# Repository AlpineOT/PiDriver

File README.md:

# PiDriver
KiCad Raspberry Pi Solenoid Driver Board

Alpine designed this RPi add-on board to drive solenoids for test automation; however, it's a generic 10-channel MOSFET board that could also be used to drive relays, LEDS, DC motors, etc.

## Features

* Controls up to 10 solenoids (though the number that can be simultaneously activated will depend upon the solenoid and capacity of your power supply)
* 2 of the 10 channels have PWM capability
* Designed for a 9-24V power input and, thus, 9-24V solenoids
* On-board flyback protection for inductive loads
* Designed for fast solenoid switching

## Fabrication

See the README_FAB.txt for notes on how the board is fabricated. Fabrication packages can be found on the [Releases](https://github.com/AlpineOT/PiDriver/releases) tab in the Github repo.

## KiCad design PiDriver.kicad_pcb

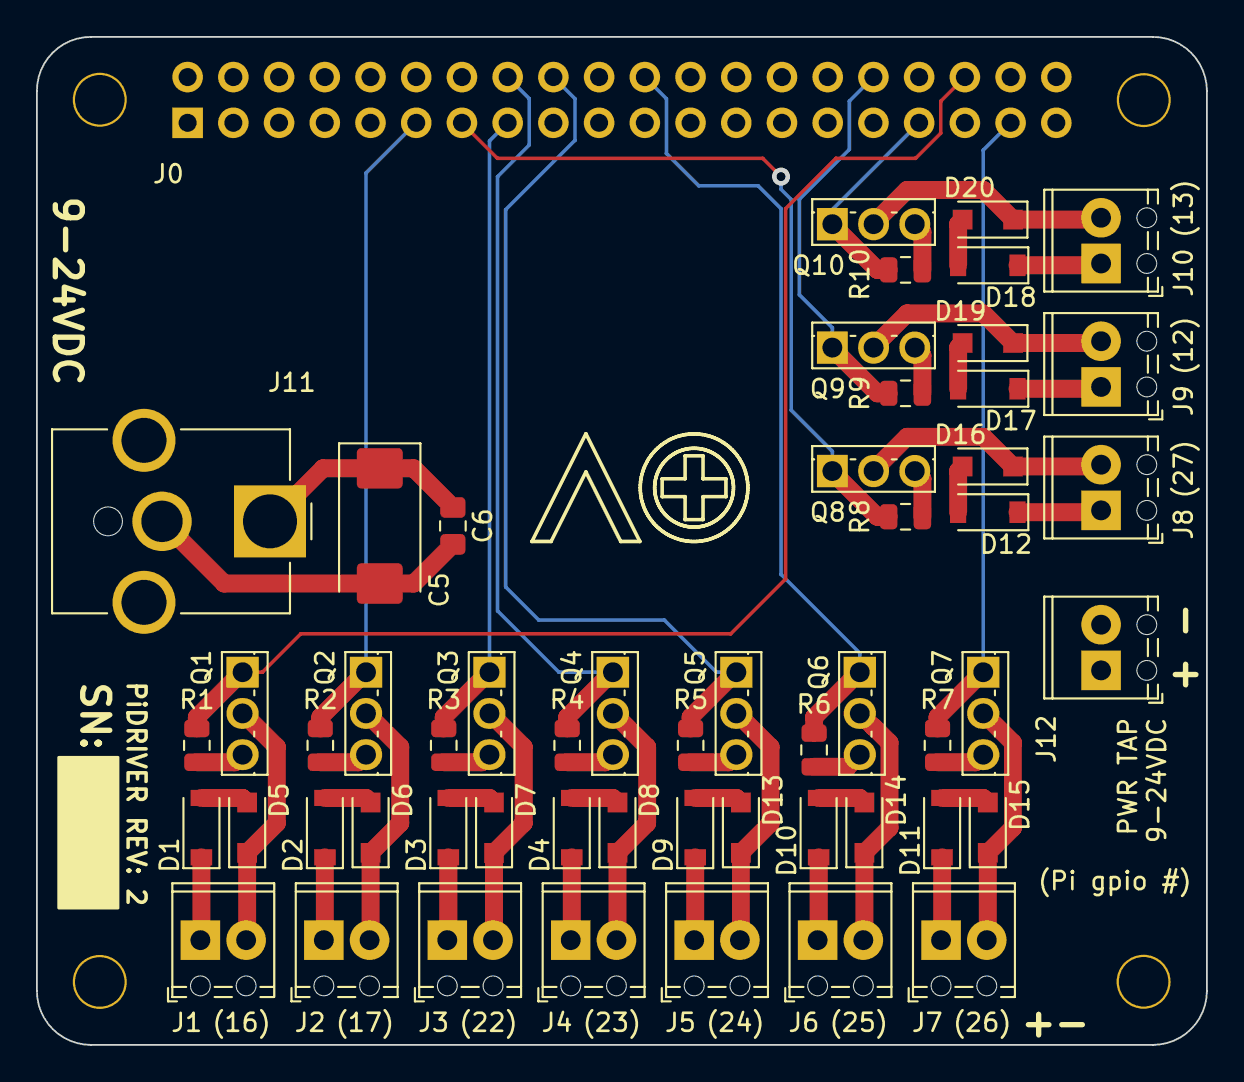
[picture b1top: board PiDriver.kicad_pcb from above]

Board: 4 copper layers, 65.0 x 56.0 mm, 60 parts (1 on the bottom side), 32 nets.

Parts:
C5: 100uF; CP_EIA-7343-43_Kemet-X_Pad2.25x2.55mm_HandSolder
C6: DNP; C_0805_2012Metric_Pad1.15x1.40mm_HandSolder
D1, D2, D3, D4, D9, D10, D11, D12, D17, D18: 1N4448W; D_SOD-123
D5, D6, D7, D8, D13, D14, D15, D16, D19, D20: DZ2W39000L; D_SOD-123F
J0: Raspberry_Pi_2_3; PinSocket_2x20_P2.54mm_Vertical
J1, J2, J3, J4, J5, J6, J7, J8, J9, J10, J12: Screw_Terminal_01x02; TerminalBlock_Phoenix_MPT-0,5-2-2.54_1x02_P2.54mm_Horizontal
J11: Jack-DC; BarrelJack_CUI_PJ-063AH_Horizontal_CircularHoles
LOGO1: AlpineLogo
MH1, MH2, MH3, MH4: MountingHole; NPTH_3mm_ID
Q1, Q2, Q3, Q4, Q5, Q6, Q7, Q8, Q9, Q10: IRLU024NPBF; TO-251-3_Vertical
R1, R2, R3, R4, R5, R6, R7, R8, R9, R10: 47K; R_0805_2012Metric

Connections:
/DRIVER_1: J0.36, Q1.1, R1.1
/DRIVER_2: J0.11, Q2.1, R2.1
/DRIVER_3: J0.15, Q3.1, R3.1
/DRIVER_4: J0.16, Q4.1, R4.1
/DRIVER_5: J0.18, Q5.1, R5.1
/DRIVER_6: J0.22, Q6.1, R6.1
/DRIVER_7: J0.37, Q7.1, R7.1
/DRIVER_8: J0.13, Q8.1, R8.1
/DRIVER_9: J0.32, Q9.1, R9.1
/DRIVER_10: J0.33, Q10.1, R10.1
GND: C5.2, C6.2, J0.6, J0.9, J0.14, J0.20, J0.25, J0.30, J0.34, J0.39, J11.2, J12.2, Q1.3, Q2.3, Q3.3, Q4.3, Q5.3, Q6.3, Q7.3, Q8.3, Q9.3, Q10.3, R1.2, R2.2, R3.2, R4.2, R5.2, R6.2, R7.2, R8.2, R9.2, R10.2
unnamed: D1.2, D5.2
unnamed: D2.2, D6.2
unnamed: D3.2, D7.2
unnamed: D4.2, D8.2
unnamed: D5.1, J1.2, Q1.2
unnamed: D6.1, J2.2, Q2.2
unnamed: D7.1, J3.2, Q3.2
unnamed: D8.1, J4.2, Q4.2
unnamed: D10.2, D14.2
unnamed: D11.2, D15.2
unnamed: D12.2, D16.2
unnamed: D13.1, J5.2, Q5.2
unnamed: D9.2, D13.2
unnamed: D14.1, J6.2, Q6.2
unnamed: D15.1, J7.2, Q7.2
unnamed: D16.1, J8.2, Q8.2
unnamed: D17.2, D19.2
unnamed: D18.2, D20.2
unnamed: D19.1, J9.2, Q9.2
unnamed: D20.1, J10.2, Q10.2
VCC: C5.1, C6.1, D1.1, D2.1, D3.1, D4.1, D9.1, D10.1, D11.1, D12.1, D17.1, D18.1, J1.1, J2.1, J3.1, J4.1, J5.1, J6.1, J7.1, J8.1, J9.1, J10.1, J11.1, J12.1

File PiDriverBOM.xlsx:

PCBA Name: |  | PiDriver
PCBA Revision: |  | 2
Item # | Quantity | Reference Designator | Manufacturer | Manufacturer Part Number | Description/Value | Vendor | Vendor Part Number | Notes
1 | 1 | C5 | KEMET | T491X107K025AT | CAP TANT 100UF 25V 10% 2917 | Digikey | 399-8410-1-ND
2 | 1 | C6 | DNP | DNP | DNP | DNP | DNP | DNP
3 | 10 | D1, D2, D3, D4, D9, D10, D11, D12, D17, D18 | Micro Commercial Co | 1N4448W-TP | DIODE GEN PURP 75V 250MA SOD123 | Digikey | 1N4448WTPMSCT-ND
4 | 10 | D5, D6, D7, D8, D13, D14, D15, D16, D19, D20 | Panasonic Electronic Components | DZ2W39000L | DIODE ZENER 39V 1W MINI2 | Digikey | DZ2W39000LCT-ND
5 | 1 | J0 | Harwin Inc. | M20-7832046 | DIL VERTICAL PC TAIL SOCKET ASSY | Digikey | 952-2150-ND
6 | 11 | J1, J2, J3, J4, J5, J6, J7, J8, J9, J10, J12 | Phoenix Contact | 1725656 | CONN TERM BLOCK 2.54MM 2POS | Digikey | 277-1273-ND
7 | 1 | J11 | CUI Inc. | PJ-063AH | CONN PWR JACK 2X5.5MM SOLDER | Digikey | CP-063AH-ND
8 | 10 | Q1, Q2, Q3, Q4, Q5, Q6, Q7, Q8, Q9, Q10 | Infineon Technologies | IRLU024NPBF | MOSFET N-CH 55V 17A I-PAK | Digikey | IRLU024NPBF-ND
9 | 10 | R1, R2, R3, R4, R5, R6, R7, R8, R9, R10 | Yageo | RC0805FR-0747KL | RES SMD 47K OHM 1% 1/8W 0805 | Digikey | 311-47.0KCRCT-ND

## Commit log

2018-08-24 First board revision
2018-08-29 Update fab notes to allow vendor to choose solder mask finish.
    Our vendor can't do matte white finish. Updating fab notes to indicate
    our preference of matte, but also allow semi-gloss and gloss.
2018-09-06 Removed 5V linear regulator because it generated too much heat.
    The 5V linear regulator generated a ton of heat right above the Pi
    processor, which caused it to thermally-overload and reset. So, we won't
    try to power the Pi from this board for now. In the future, we could use
    a more efficient switching supply that wouldn't generate as much heat.
    But, we can separately power the Pi via USB for now.
2018-09-12 Tweaked silkscreen for readability
2018-09-13 Added BOM and updated readme.
2018-09-13 Added notes about fabrication to readme.
2019-01-03 Minor README.md correction
    Removed mention of powering the Raspberry Pi since that's been removed for thermal reasons.

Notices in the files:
PiDriver.kicad_pcb:
Copyright 2018 by Alpine Oral Tech. Inc. All Rights Reserved.
